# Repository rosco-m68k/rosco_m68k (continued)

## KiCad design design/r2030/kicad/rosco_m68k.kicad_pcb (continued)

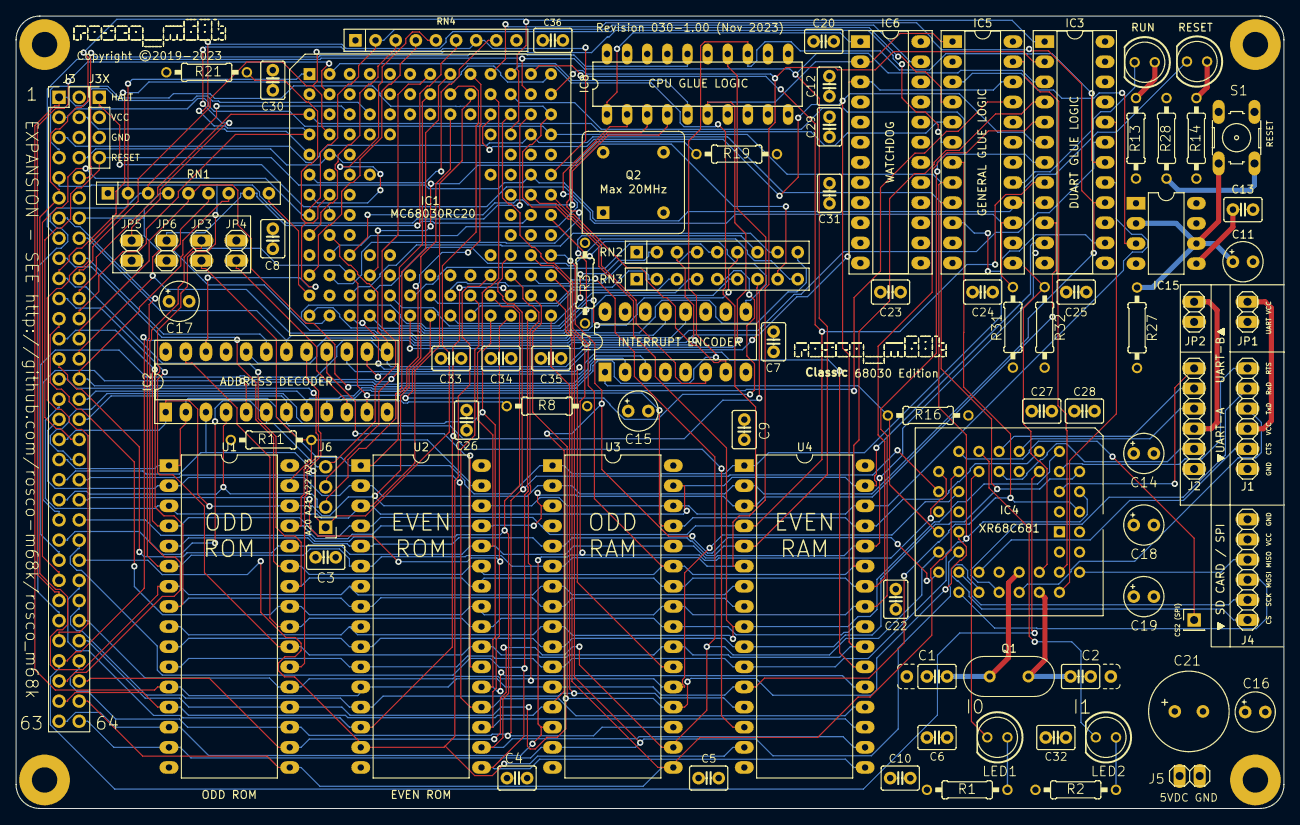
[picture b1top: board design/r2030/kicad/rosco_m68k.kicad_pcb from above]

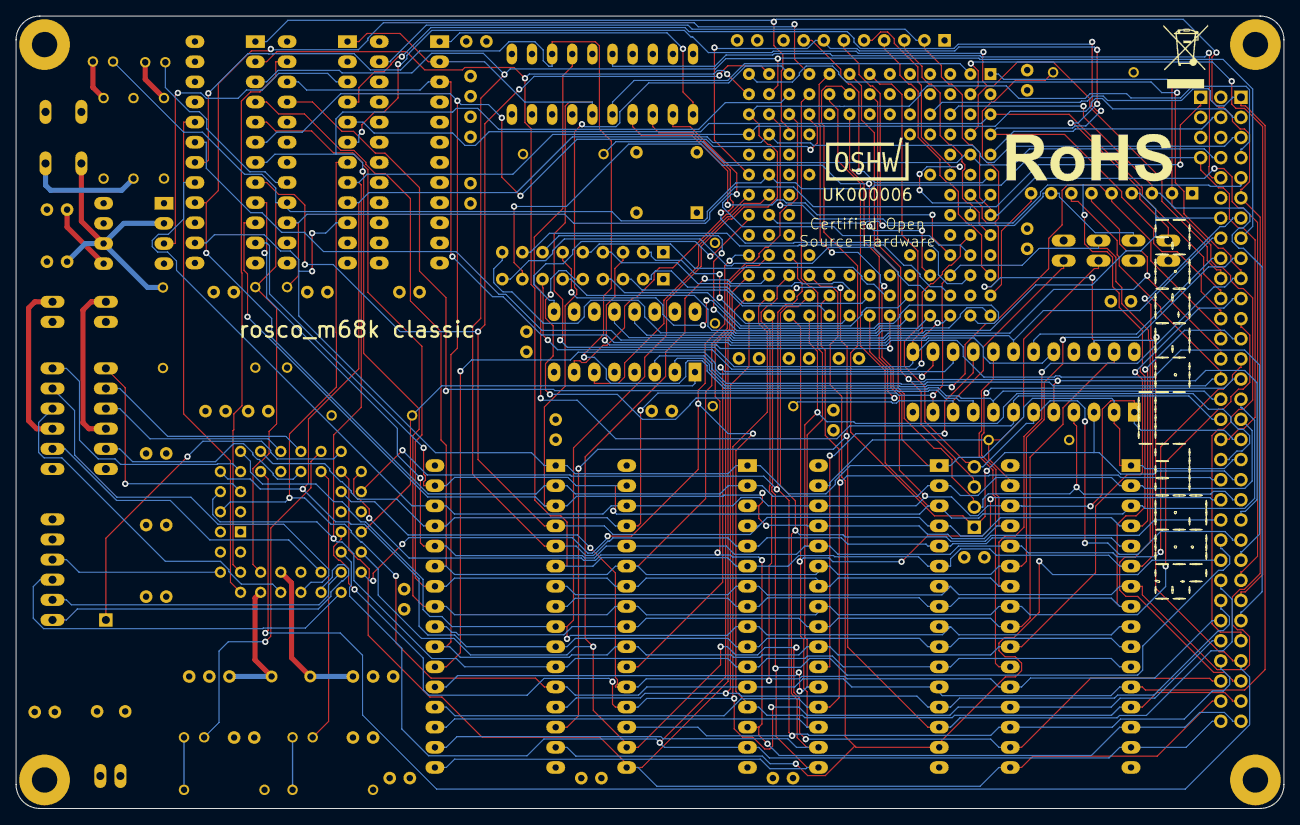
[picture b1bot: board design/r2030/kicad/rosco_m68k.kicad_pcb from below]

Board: 4 copper layers, 160.0 x 100.0 mm, 97 parts (3 on the bottom side), 135 nets.

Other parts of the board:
OSHW_Mono_0.25_Scale: UK000006; OSHW_Mono_0.25_Scale
rohs: RoHS-Logo_6mm_SilkScreen
rosco_m68k, rosco_m68k_mid: SM-rosco_m68k_logo
weee: WEEE-Logo_5.6x8mm_SilkScreen

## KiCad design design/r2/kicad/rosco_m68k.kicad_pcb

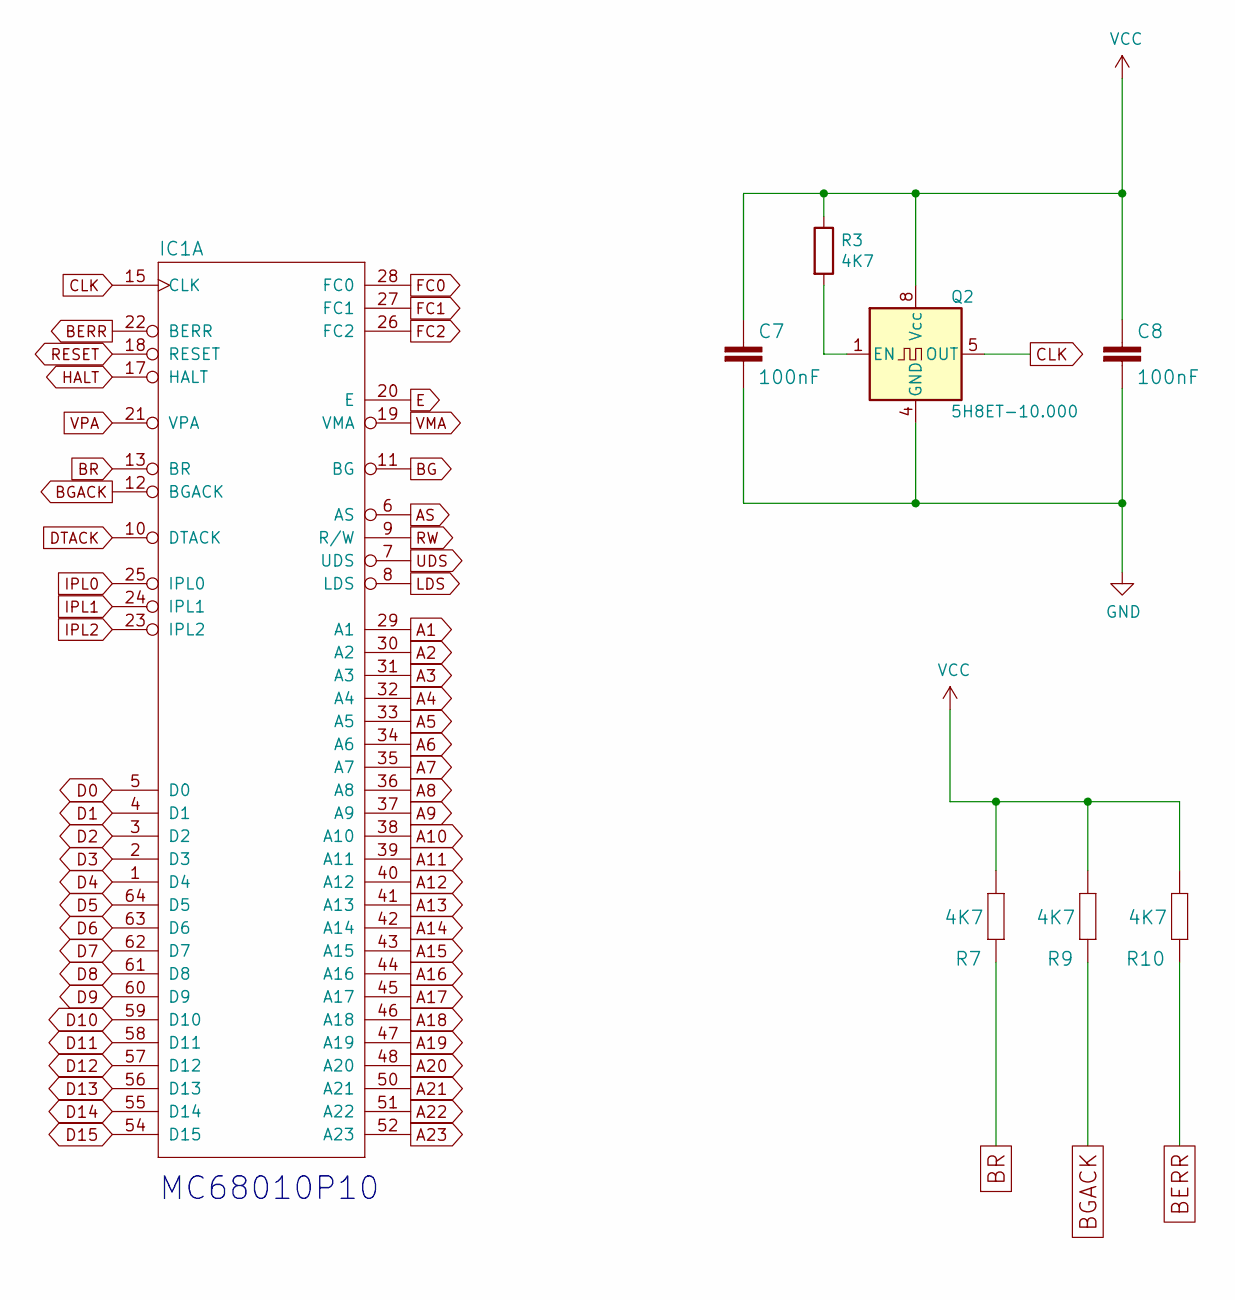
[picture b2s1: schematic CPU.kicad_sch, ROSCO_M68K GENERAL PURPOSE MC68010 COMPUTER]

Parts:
C7, C8: 100nF; C2.5-3
IC1: MC68010P10; DIL64
Q2: 5H8ET-10.000; Oscillator_DIP-8
R3, R7, R9, R10: 4K7; 0207_10

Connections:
A1: IC1.29 (A1); also elsewhere on the board
A2: IC1.30 (A2); also elsewhere on the board
A3: IC1.31 (A3); also elsewhere on the board
A4: IC1.32 (A4); also elsewhere on the board
A5: IC1.33 (A5); also elsewhere on the board
A6: IC1.34 (A6); also elsewhere on the board
A7: IC1.35 (A7); also elsewhere on the board
A8: IC1.36 (A8); also elsewhere on the board
A9: IC1.37 (A9); also elsewhere on the board
A10: IC1.38 (A10); also elsewhere on the board
A11: IC1.39 (A11); also elsewhere on the board
A12: IC1.40 (A12); also elsewhere on the board
A13: IC1.41 (A13); also elsewhere on the board
A14: IC1.42 (A14); also elsewhere on the board
A15: IC1.43 (A15); also elsewhere on the board
A16: IC1.44 (A16); also elsewhere on the board
A17: IC1.45 (A17); also elsewhere on the board
A18: IC1.46 (A18); also elsewhere on the board
A19: IC1.47 (A19); also elsewhere on the board
A20: IC1.48 (A20); also elsewhere on the board
A21: IC1.50 (A21); also elsewhere on the board
A22: IC1.51 (A22); also elsewhere on the board
A23: IC1.52 (A23); also elsewhere on the board
AS: IC1.6 (AS); also elsewhere on the board
BERR: IC1.22 (BERR), R10.1; also elsewhere on the board
BG: IC1.11 (BG); also elsewhere on the board
BGACK: IC1.12 (BGACK), R9.1; also elsewhere on the board
BR: IC1.13 (BR), R7.1; also elsewhere on the board
CLK: IC1.15 (CLK), Q2.5 (OUT); also elsewhere on the board
D0: IC1.5 (D0); also elsewhere on the board
D1: IC1.4 (D1); also elsewhere on the board
D2: IC1.3 (D2); also elsewhere on the board
D3: IC1.2 (D3); also elsewhere on the board
D4: IC1.1 (D4); also elsewhere on the board
D5: IC1.64 (D5); also elsewhere on the board
D6: IC1.63 (D6); also elsewhere on the board
D7: IC1.62 (D7); also elsewhere on the board
D8: IC1.61 (D8); also elsewhere on the board
D9: IC1.60 (D9); also elsewhere on the board
D10: IC1.59 (D10); also elsewhere on the board
D11: IC1.58 (D11); also elsewhere on the board
D12: IC1.57 (D12); also elsewhere on the board
D13: IC1.56 (D13); also elsewhere on the board
D14: IC1.55 (D14); also elsewhere on the board
D15: IC1.54 (D15); also elsewhere on the board
DTACK: IC1.10 (DTACK); also elsewhere on the board
E: IC1.20 (E); also elsewhere on the board
FC0: IC1.28 (FC0); also elsewhere on the board
FC1: IC1.27 (FC1); also elsewhere on the board
FC2: IC1.26 (FC2); also elsewhere on the board
GND: C7.2, C8.2, IC1.16 (GND@1), IC1.53 (GND@2), Q2.4 (GND); also elsewhere on the board
HALT: IC1.17 (HALT); also elsewhere on the board
IPL0: IC1.25 (IPL0); also elsewhere on the board
IPL1: IC1.24 (IPL1); also elsewhere on the board
IPL2: IC1.23 (IPL2); also elsewhere on the board
LDS: IC1.8 (LDS); also elsewhere on the board
unnamed: Q2.1 (EN), R3.2
RESET: IC1.18 (RESET); also elsewhere on the board
RW: IC1.9 (R/W); also elsewhere on the board
UDS: IC1.7 (UDS); also elsewhere on the board
VCC: C7.1, C8.1, IC1.14 (VCC@1), IC1.49 (VCC@2), Q2.8 (Vcc), R3.1, R7.2, R9.2, R10.2; also elsewhere on the board
VMA: IC1.19 (VMA); also elsewhere on the board
VPA: IC1.21 (VPA); also elsewhere on the board

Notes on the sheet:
MC68010P10

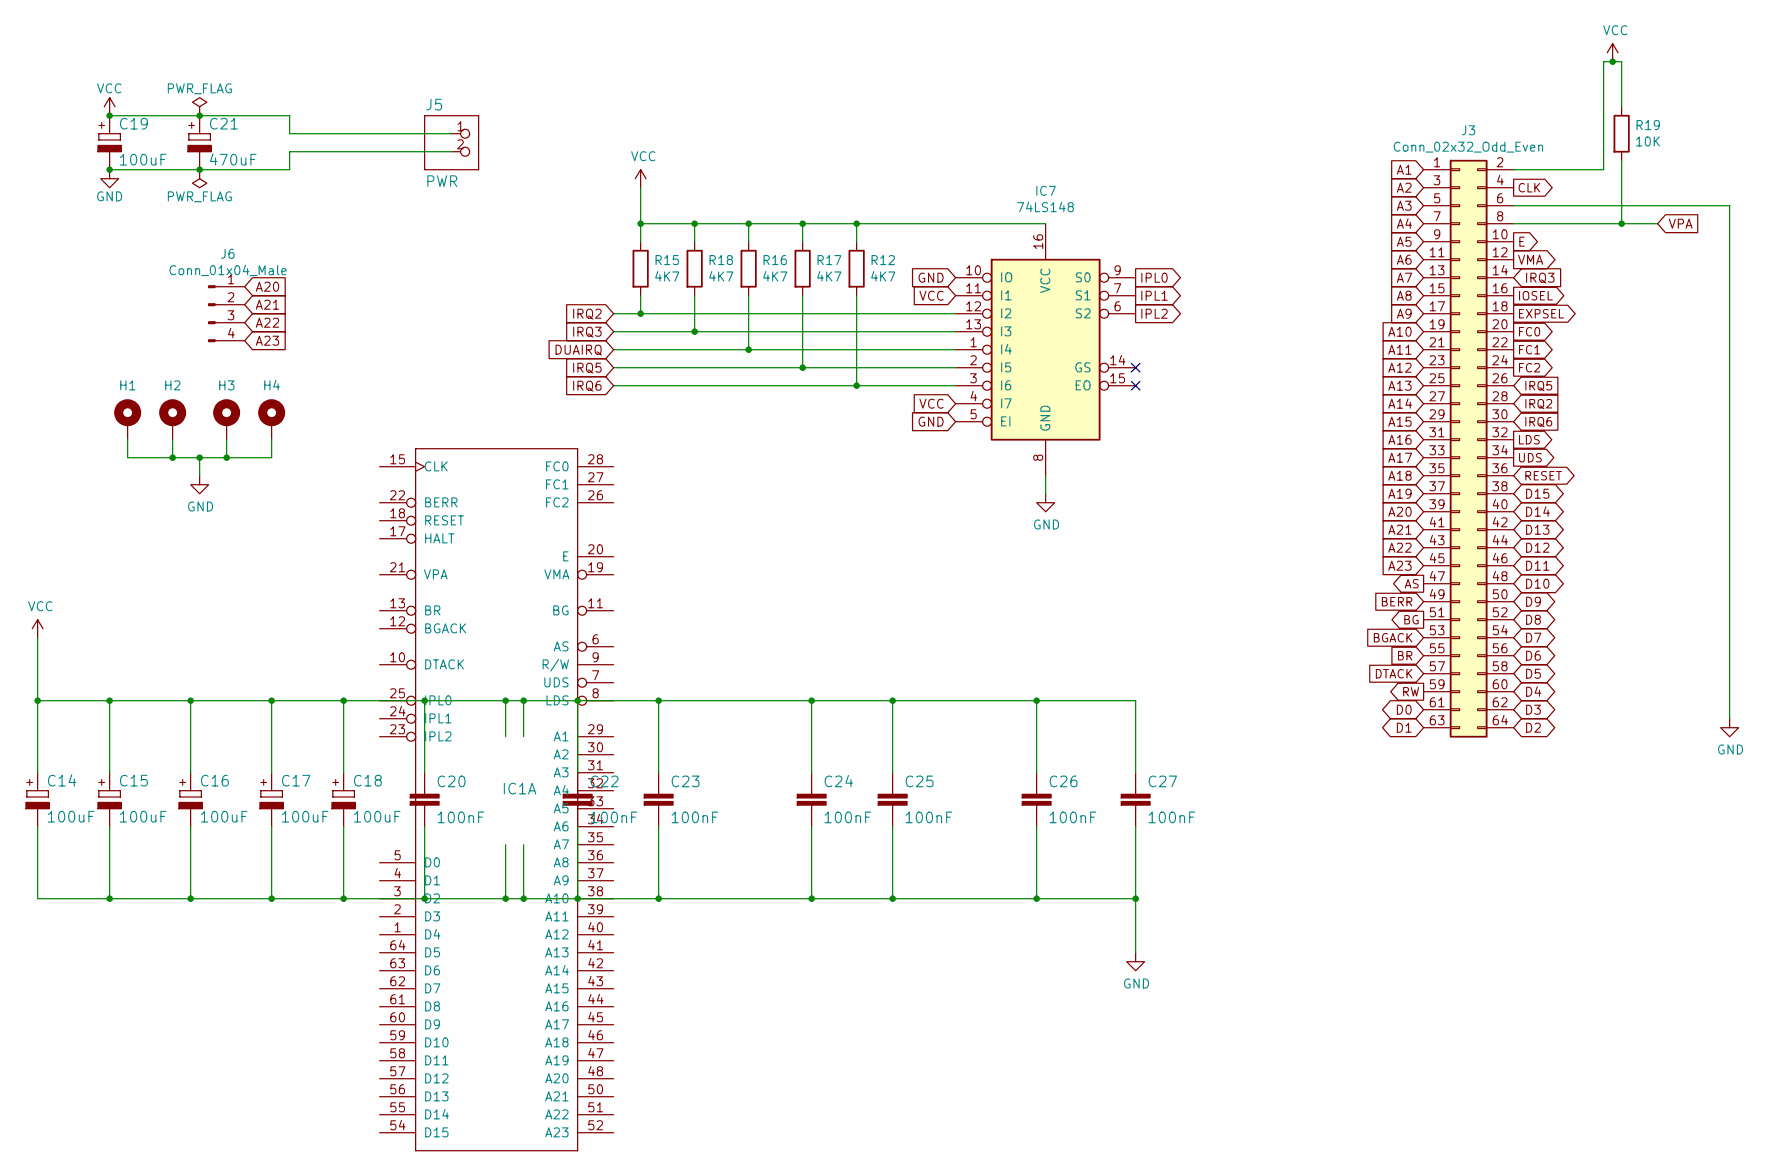
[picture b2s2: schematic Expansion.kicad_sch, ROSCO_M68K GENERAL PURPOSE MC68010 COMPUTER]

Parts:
C14, C15, C16, C17, C18, C19: 100uF; E2,5-5
C20, C22, C23, C24, C25, C26, C27: 100nF; C2.5-3
C21: 470uF; E3,5-10
H1, H2, H3, H4: MountingHole; MountingHole_3.2mm_M3_Pad
IC1: MC68010P10; DIL64
IC7: 74LS148; DIP-16_W7.62mm_LongPads
J3: Conn_02x32_Odd_Even; PinHeader_2x32_P2.54mm_Vertical
J5: PWR; 1X02
J6: Conn_01x04_Male; PinHeader_1x04_P2.54mm_Vertical
R12, R15, R16, R17, R18: 4K7; 0207_10
R19: 10K; 0207_10

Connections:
A1: IC1.29 (A1), J3.1; also elsewhere on the board
A2: IC1.30 (A2), J3.3; also elsewhere on the board
A3: IC1.31 (A3), J3.5; also elsewhere on the board
A4: IC1.32 (A4), J3.7; also elsewhere on the board
A5: IC1.33 (A5), J3.9; also elsewhere on the board
A6: IC1.34 (A6), J3.11; also elsewhere on the board
A7: IC1.35 (A7), J3.13; also elsewhere on the board
A8: IC1.36 (A8), J3.15; also elsewhere on the board
A9: IC1.37 (A9), J3.17; also elsewhere on the board
A10: IC1.38 (A10), J3.19; also elsewhere on the board
A11: IC1.39 (A11), J3.21; also elsewhere on the board
A12: IC1.40 (A12), J3.23; also elsewhere on the board
A13: IC1.41 (A13), J3.25; also elsewhere on the board
A14: IC1.42 (A14), J3.27; also elsewhere on the board
A15: IC1.43 (A15), J3.29; also elsewhere on the board
A16: IC1.44 (A16), J3.31; also elsewhere on the board
A17: IC1.45 (A17), J3.33; also elsewhere on the board
A18: IC1.46 (A18), J3.35; also elsewhere on the board
A19: IC1.47 (A19), J3.37; also elsewhere on the board
A20: IC1.48 (A20), J3.39, J6.1; also elsewhere on the board
A21: IC1.50 (A21), J3.41, J6.2; also elsewhere on the board
A22: IC1.51 (A22), J3.43, J6.3; also elsewhere on the board
A23: IC1.52 (A23), J3.45, J6.4; also elsewhere on the board
AS: IC1.6 (AS), J3.47; also elsewhere on the board
BERR: IC1.22 (BERR), J3.49; also elsewhere on the board
BG: IC1.11 (BG), J3.51
BGACK: IC1.12 (BGACK), J3.53; also elsewhere on the board
BR: IC1.13 (BR), J3.55; also elsewhere on the board
CLK: IC1.15 (CLK), J3.4; also elsewhere on the board
D0: IC1.5 (D0), J3.61; also elsewhere on the board
D1: IC1.4 (D1), J3.63; also elsewhere on the board
D2: IC1.3 (D2), J3.64; also elsewhere on the board
D3: IC1.2 (D3), J3.62; also elsewhere on the board
D4: IC1.1 (D4), J3.60; also elsewhere on the board
D5: IC1.64 (D5), J3.58; also elsewhere on the board
D6: IC1.63 (D6), J3.56; also elsewhere on the board
D7: IC1.62 (D7), J3.54; also elsewhere on the board
D8: IC1.61 (D8), J3.52; also elsewhere on the board
D9: IC1.60 (D9), J3.50; also elsewhere on the board
D10: IC1.59 (D10), J3.48; also elsewhere on the board
D11: IC1.58 (D11), J3.46; also elsewhere on the board
D12: IC1.57 (D12), J3.44; also elsewhere on the board
D13: IC1.56 (D13), J3.42; also elsewhere on the board
D14: IC1.55 (D14), J3.40; also elsewhere on the board
D15: IC1.54 (D15), J3.38; also elsewhere on the board
DTACK: IC1.10 (DTACK), J3.57; also elsewhere on the board
DUAIRQ: IC7.1 (I4), R16.2; also elsewhere on the board
E: IC1.20 (E), J3.10
EXPSEL: J3.18; also elsewhere on the board
FC0: IC1.28 (FC0), J3.20; also elsewhere on the board
FC1: IC1.27 (FC1), J3.22; also elsewhere on the board
FC2: IC1.26 (FC2), J3.24; also elsewhere on the board
GND: C14.-, C15.-, C16.-, C17.-, C18.-, C19.-, C20.2, C21.-, C22.2, C23.2, C24.2, C25.2, C26.2, C27.2, H1.1, H2.1, H3.1, H4.1, IC1.16 (GND@1), IC1.53 (GND@2), IC7.5 (EI), IC7.8 (GND), IC7.10 (IO), J3.6, J5.2; also elsewhere on the board
HALT: IC1.17 (HALT); also elsewhere on the board
IOSEL: J3.16; also elsewhere on the board
IPL0: IC1.25 (IPL0), IC7.9 (S0)
IPL1: IC1.24 (IPL1), IC7.7 (S1)
IPL2: IC1.23 (IPL2), IC7.6 (S2)
IRQ2: IC7.12 (I2), J3.28, R15.2
IRQ3: IC7.13 (I3), J3.14, R18.2
IRQ5: IC7.2 (I5), J3.26, R17.2
IRQ6: IC7.3 (I6), J3.30, R12.2
LDS: IC1.8 (LDS), J3.32; also elsewhere on the board
RESET: IC1.18 (RESET), J3.36; also elsewhere on the board
RW: IC1.9 (R/W), J3.59; also elsewhere on the board
UDS: IC1.7 (UDS), J3.34; also elsewhere on the board
VCC: C14.+, C15.+, C16.+, C17.+, C18.+, C19.+, C20.1, C21.+, C22.1, C23.1, C24.1, C25.1, C26.1, C27.1, IC1.14 (VCC@1), IC1.49 (VCC@2), IC7.4 (I7), IC7.11 (I1), IC7.16 (VCC), J3.2, J5.1, R12.1, R15.1, R16.1, R17.1, R18.1, R19.1; also elsewhere on the board
VMA: IC1.19 (VMA), J3.12
VPA: IC1.21 (VPA), J3.8, R19.2

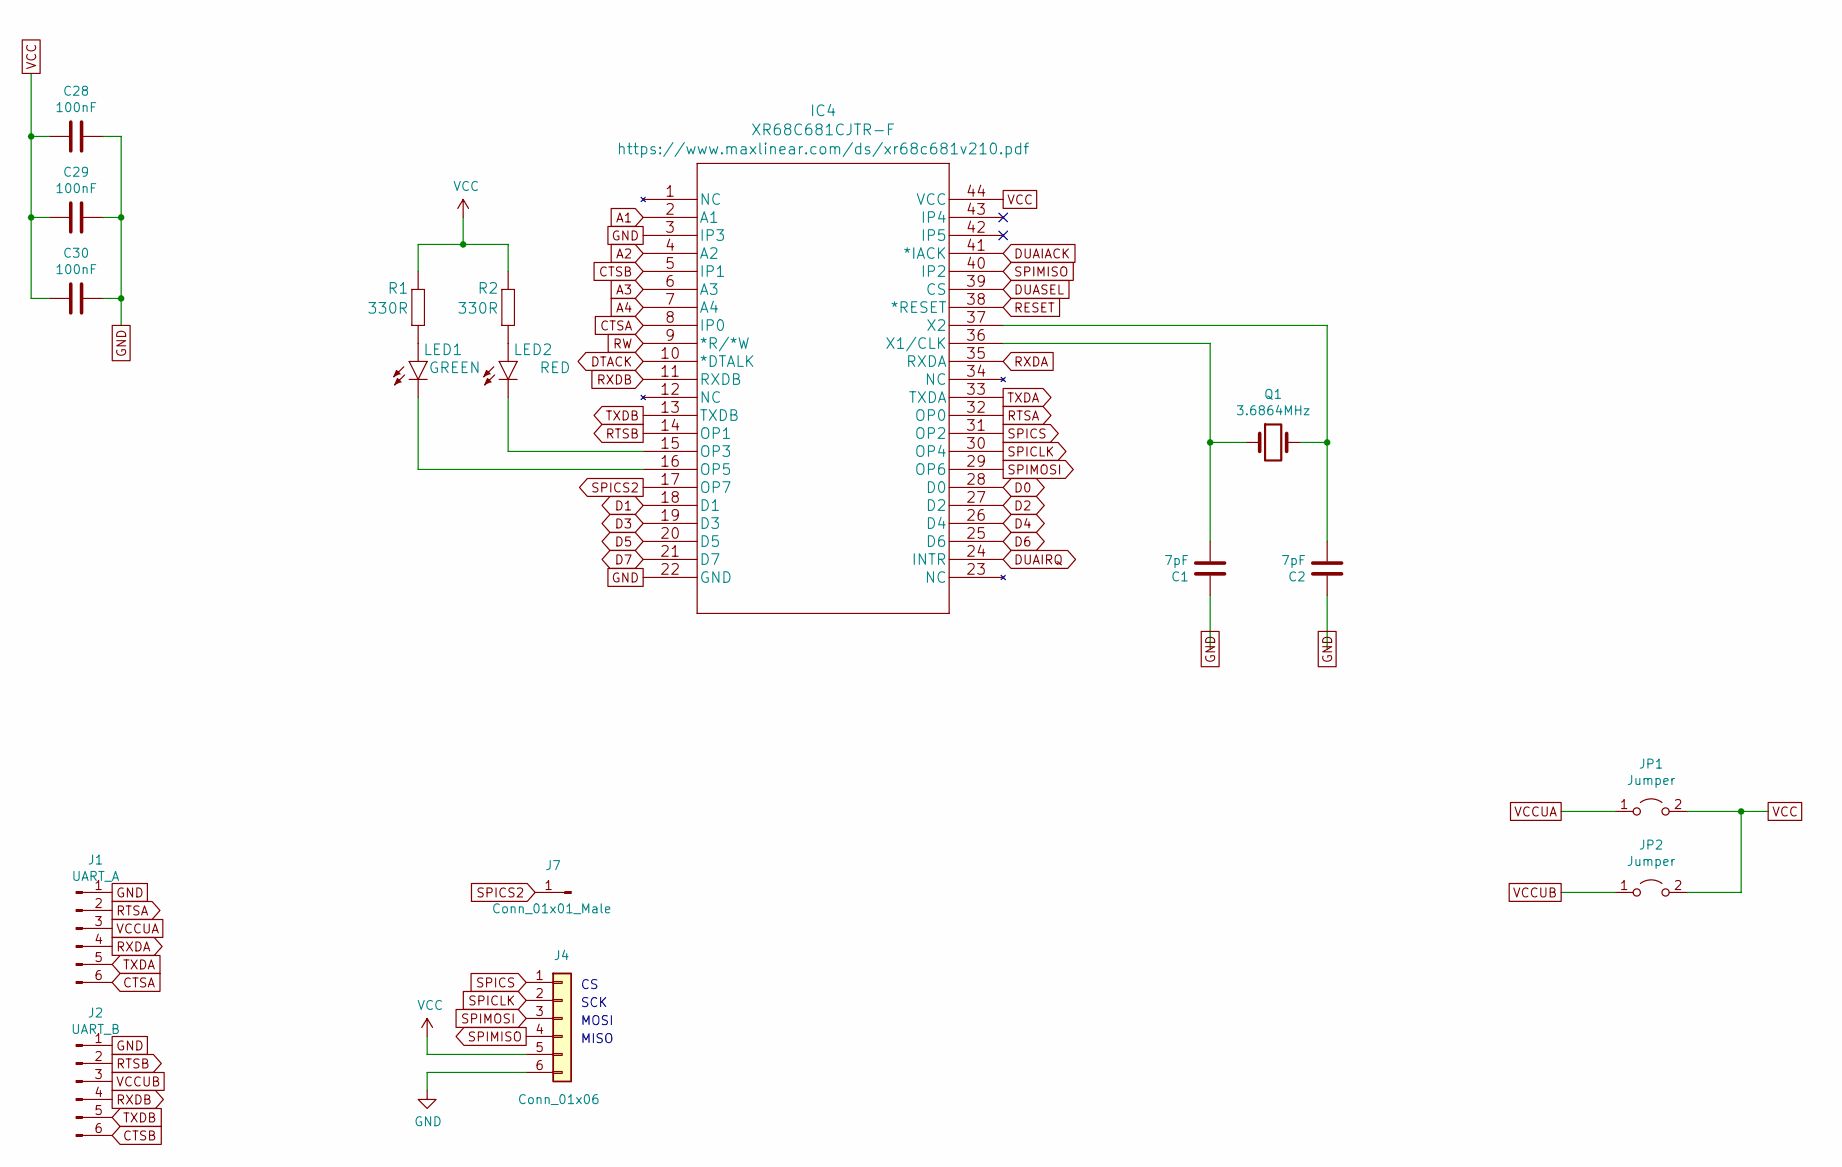
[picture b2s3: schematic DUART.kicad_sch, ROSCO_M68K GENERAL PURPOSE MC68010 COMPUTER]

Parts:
C1, C2: 7pF; C2.5_or_3.5-3
C28, C29, C30: 100nF; C2.5-3
IC4: XR68C681CJTR-F; PLCC-44_THT-Socket
J1: UART_A; 1X06
J2: UART_B; 1X06
J4: Conn_01x06; 1X06
J7: Conn_01x01_Male; PinHeader_1x01_P2.54mm_Vertical
JP1, JP2: Jumper; 1X02
LED1: GREEN; LED5MM
LED2: RED; LED5MM
Q1: 3.6864MHz; Crystal_HC49-4H_Vertical
R1, R2: 330R; 0207_10

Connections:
A1: IC4.2 (A1); also elsewhere on the board
A2: IC4.4 (A2); also elsewhere on the board
A3: IC4.6 (A3); also elsewhere on the board
A4: IC4.7 (A4); also elsewhere on the board
CTSA: IC4.8 (IP0), J1.6
CTSB: IC4.5 (IP1), J2.6
D0: IC4.28 (D0); also elsewhere on the board
D1: IC4.18 (D1); also elsewhere on the board
D2: IC4.27 (D2); also elsewhere on the board
D3: IC4.19 (D3); also elsewhere on the board
D4: IC4.26 (D4); also elsewhere on the board
D5: IC4.20 (D5); also elsewhere on the board
D6: IC4.25 (D6); also elsewhere on the board
D7: IC4.21 (D7); also elsewhere on the board
DTACK: IC4.10 (*DTALK); also elsewhere on the board
DUAIACK: IC4.41 (*IACK); also elsewhere on the board
DUAIRQ: IC4.24 (INTR); also elsewhere on the board
DUASEL: IC4.39 (CS); also elsewhere on the board
GND: C1.1, C2.1, C28.1, C29.1, C30.1, IC4.3 (IP3), IC4.22 (GND), J1.1, J2.1, J4.6; also elsewhere on the board
unnamed: C1.2, IC4.36 (X1/CLK), Q1.1
unnamed: C2.2, IC4.37 (X2), Q1.2
unnamed: IC4.15 (OP3), LED2.K (C)
unnamed: IC4.16 (OP5), LED1.K (C)
unnamed: LED1.A, R1.1
unnamed: LED2.A, R2.1
RESET: IC4.38 (*RESET); also elsewhere on the board
RTSA: IC4.32 (OP0), J1.2
RTSB: IC4.14 (OP1), J2.2
RW: IC4.9 (*R/*W); also elsewhere on the board
RXDA: IC4.35 (RXDA), J1.4
RXDB: IC4.11 (RXDB), J2.4
SPICLK: IC4.30 (OP4), J4.2
SPICS: IC4.31 (OP2), J4.1
SPICS2: IC4.17 (OP7), J7.1
SPIMISO: IC4.40 (IP2), J4.4
SPIMOSI: IC4.29 (OP6), J4.3
TXDA: IC4.33 (TXDA), J1.5
TXDB: IC4.13 (TXDB), J2.5
VCC: C28.2, C29.2, C30.2, IC4.44 (VCC), J4.5, JP1.2 (B), JP2.2 (B), R1.2, R2.2; also elsewhere on the board
VCCUA: J1.3, JP1.1 (A)
VCCUB: J2.3, JP2.1 (A)

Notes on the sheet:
MISO
SCK
MOSI

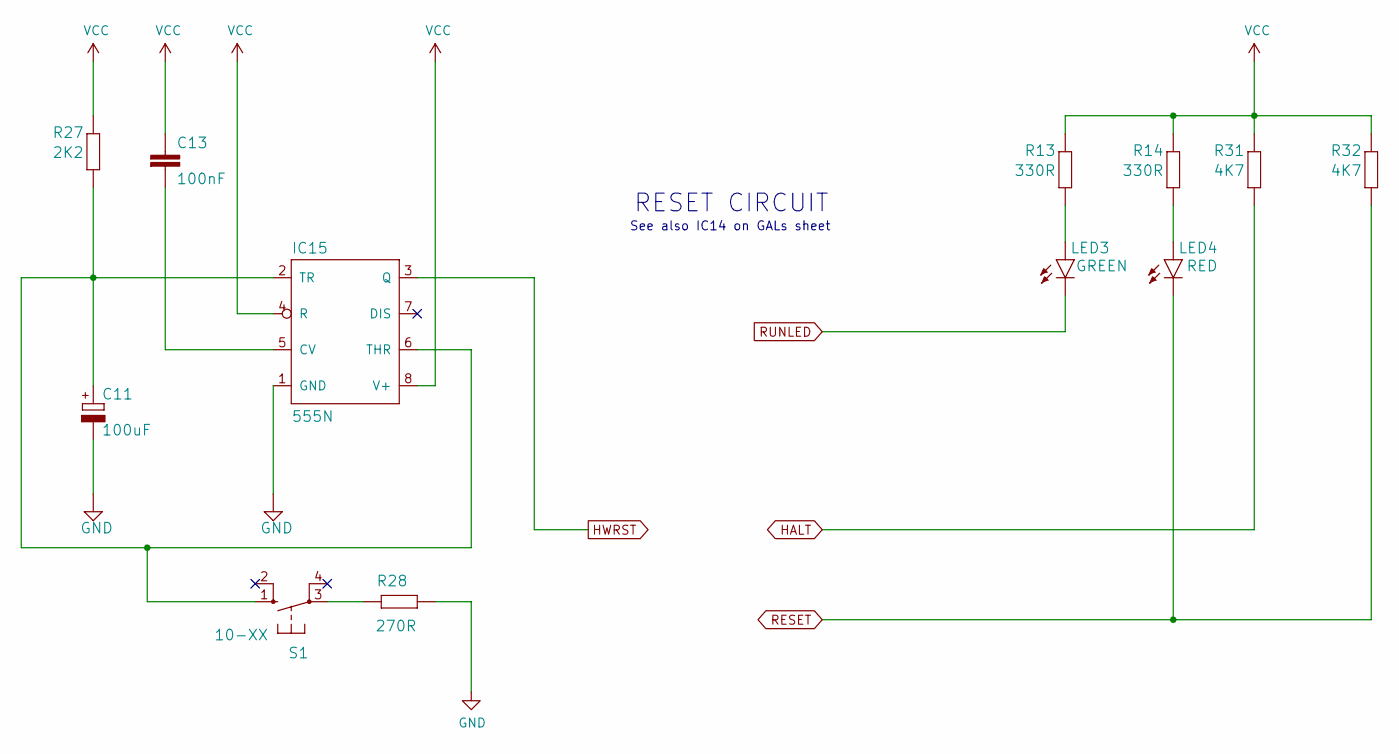
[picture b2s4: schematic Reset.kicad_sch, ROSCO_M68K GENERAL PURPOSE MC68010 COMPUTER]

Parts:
C11: 100uF; E2,5-5
C13: 100nF; C2.5-3
IC15: 555N; DIP-8_W7.62mm_LongPads
LED3: GREEN; LED5MM
LED4: RED; LED5MM
R13, R14: 330R; 0207_10
R27: 2K2; 0207_10
R28: 270R; 0207_10
R31, R32: 4K7; 0207_10
S1: 10-XX; B3F-10XX

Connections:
GND: C11.-, IC15.1 (GND), R28.1; also elsewhere on the board
HALT: R31.1; also elsewhere on the board
HWRST: IC15.3 (Q); also elsewhere on the board
unnamed: C11.+, IC15.2 (TR), IC15.6 (THR), R27.1, S1.1 (S)
unnamed: C13.2, IC15.5 (CV)
unnamed: LED3.A, R13.1
unnamed: LED4.A, R14.1
unnamed: R28.2, S1.3
RESET: LED4.K (C), R32.1; also elsewhere on the board
RUNLED: LED3.K (C); also elsewhere on the board
VCC: C13.1, IC15.4 (R), IC15.8 (V+), R13.2, R14.2, R27.2, R31.2, R32.2; also elsewhere on the board

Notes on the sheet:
See also IC14 on GALs sheet
RESET CIRCUIT

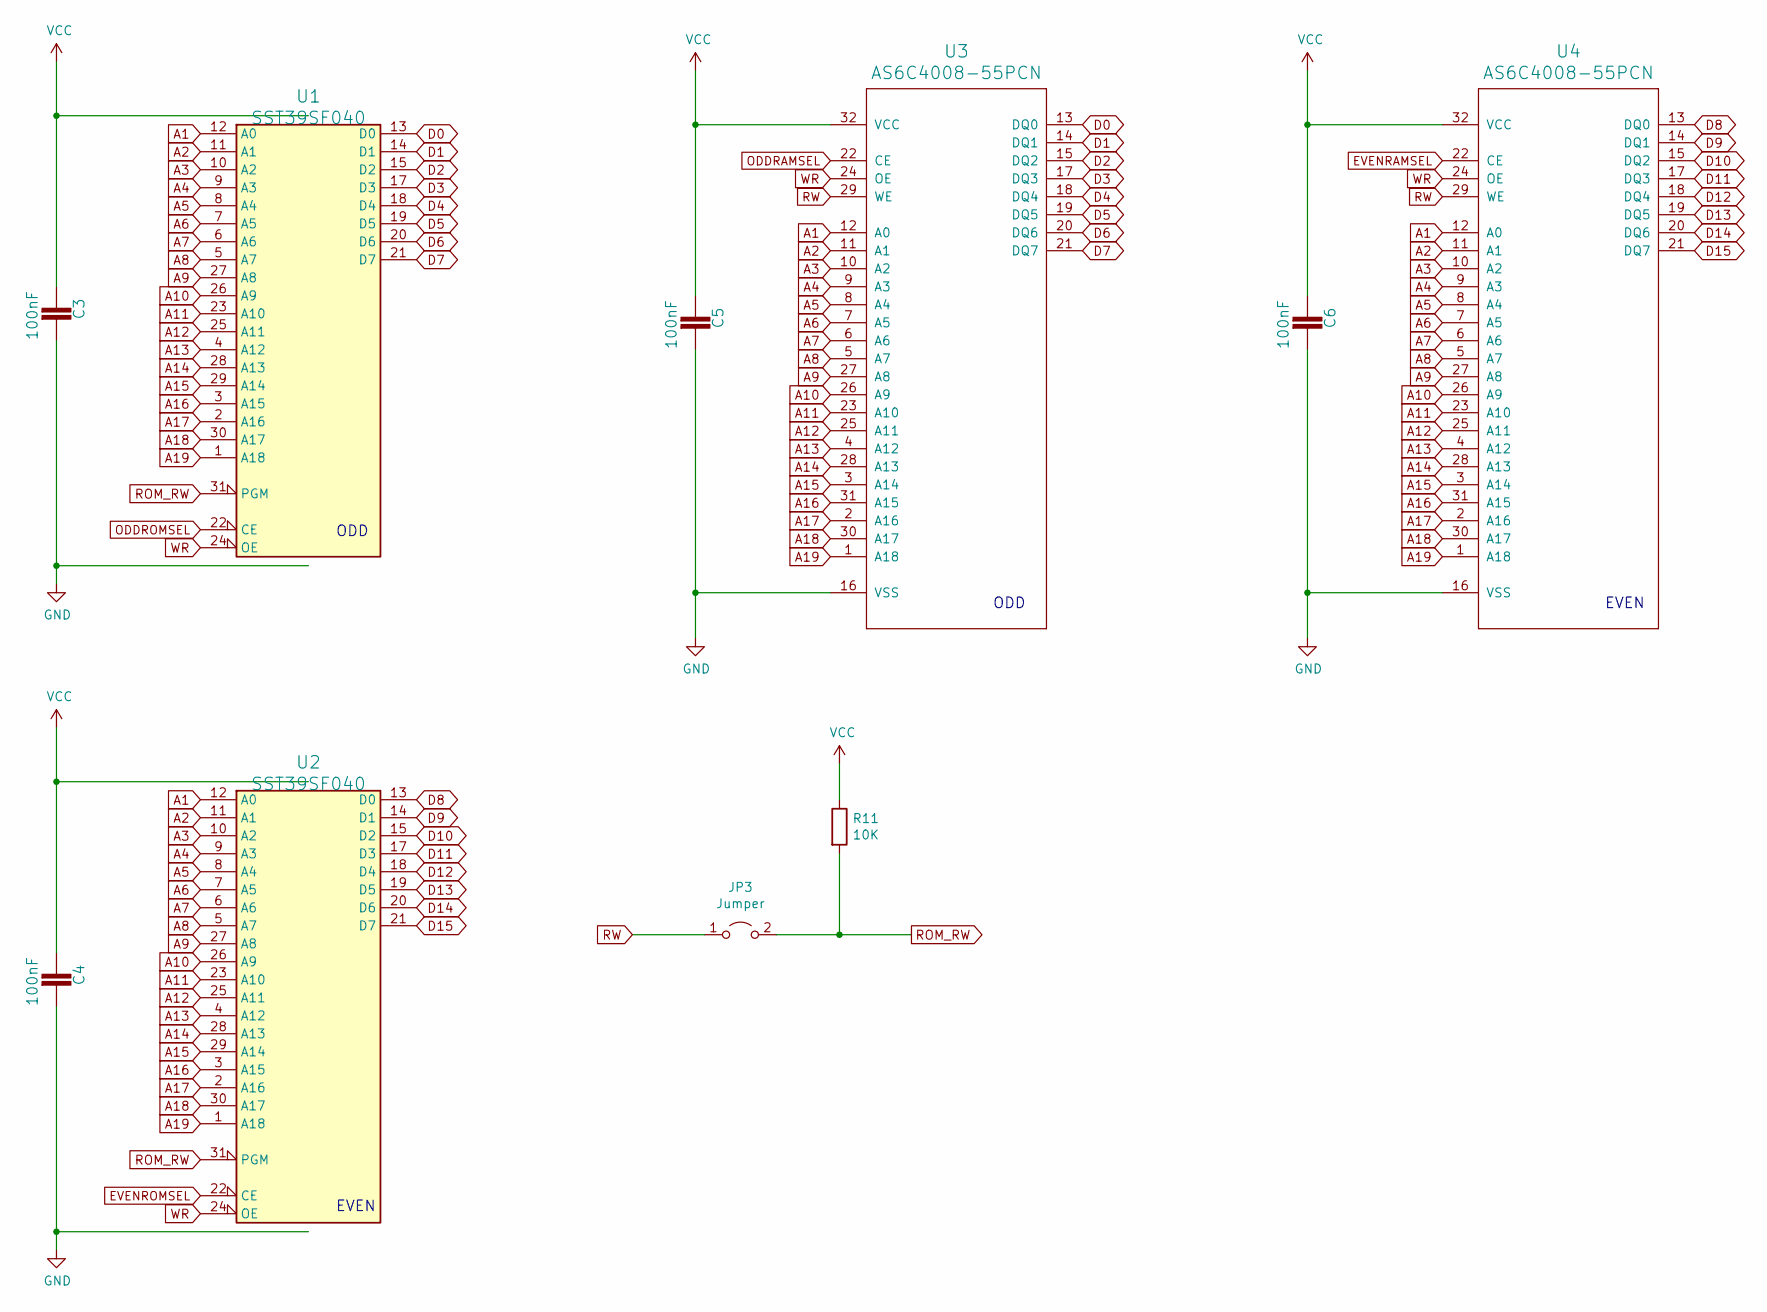
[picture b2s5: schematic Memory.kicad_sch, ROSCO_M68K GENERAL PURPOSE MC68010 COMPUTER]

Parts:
C3, C4, C5, C6: 100nF; C2.5-3
JP3: Jumper; 1X02
R11: 10K; 0207_10
U1, U2: SST39SF040; DIP-32_W15.24mm_LongPads
U3, U4: AS6C4008-55PCN; DIP-32_W15.24mm_LongPads

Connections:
A1: U1.12 (A0), U2.12 (A0), U3.12 (A0), U4.12 (A0); also elsewhere on the board
A2: U1.11 (A1), U2.11 (A1), U3.11 (A1), U4.11 (A1); also elsewhere on the board
A3: U1.10 (A2), U2.10 (A2), U3.10 (A2), U4.10 (A2); also elsewhere on the board
A4: U1.9 (A3), U2.9 (A3), U3.9 (A3), U4.9 (A3); also elsewhere on the board
A5: U1.8 (A4), U2.8 (A4), U3.8 (A4), U4.8 (A4); also elsewhere on the board
A6: U1.7 (A5), U2.7 (A5), U3.7 (A5), U4.7 (A5); also elsewhere on the board
A7: U1.6 (A6), U2.6 (A6), U3.6 (A6), U4.6 (A6); also elsewhere on the board
A8: U1.5 (A7), U2.5 (A7), U3.5 (A7), U4.5 (A7); also elsewhere on the board
A9: U1.27 (A8), U2.27 (A8), U3.27 (A8), U4.27 (A8); also elsewhere on the board
A10: U1.26 (A9), U2.26 (A9), U3.26 (A9), U4.26 (A9); also elsewhere on the board
A11: U1.23 (A10), U2.23 (A10), U3.23 (A10), U4.23 (A10); also elsewhere on the board
A12: U1.25 (A11), U2.25 (A11), U3.25 (A11), U4.25 (A11); also elsewhere on the board
A13: U1.4 (A12), U2.4 (A12), U3.4 (A12), U4.4 (A12); also elsewhere on the board
A14: U1.28 (A13), U2.28 (A13), U3.28 (A13), U4.28 (A13); also elsewhere on the board
A15: U1.29 (A14), U2.29 (A14), U3.3 (A14), U4.3 (A14); also elsewhere on the board
A16: U1.3 (A15), U2.3 (A15), U3.31 (A15), U4.31 (A15); also elsewhere on the board
A17: U1.2 (A16), U2.2 (A16), U3.2 (A16), U4.2 (A16); also elsewhere on the board
A18: U1.30 (A17), U2.30 (A17), U3.30 (A17), U4.30 (A17); also elsewhere on the board
A19: U1.1 (A18), U2.1 (A18), U3.1 (A18), U4.1 (A18); also elsewhere on the board
D0: U1.13 (D0), U3.13 (DQ0); also elsewhere on the board
D1: U1.14 (D1), U3.14 (DQ1); also elsewhere on the board
D2: U1.15 (D2), U3.15 (DQ2); also elsewhere on the board
D3: U1.17 (D3), U3.17 (DQ3); also elsewhere on the board
D4: U1.18 (D4), U3.18 (DQ4); also elsewhere on the board
D5: U1.19 (D5), U3.19 (DQ5); also elsewhere on the board
D6: U1.20 (D6), U3.20 (DQ6); also elsewhere on the board
D7: U1.21 (D7), U3.21 (DQ7); also elsewhere on the board
D8: U2.13 (D0), U4.13 (DQ0); also elsewhere on the board
D9: U2.14 (D1), U4.14 (DQ1); also elsewhere on the board
D10: U2.15 (D2), U4.15 (DQ2); also elsewhere on the board
D11: U2.17 (D3), U4.17 (DQ3); also elsewhere on the board
D12: U2.18 (D4), U4.18 (DQ4); also elsewhere on the board
D13: U2.19 (D5), U4.19 (DQ5); also elsewhere on the board
D14: U2.20 (D6), U4.20 (DQ6); also elsewhere on the board
D15: U2.21 (D7), U4.21 (DQ7); also elsewhere on the board
EVENRAMSEL: U4.22 (CE); also elsewhere on the board
EVENROMSEL: U2.22 (CE); also elsewhere on the board
GND: C3.2, C4.2, C5.2, C6.2, U1.16 (GND), U2.16 (GND), U3.16 (VSS), U4.16 (VSS); also elsewhere on the board
ODDRAMSEL: U3.22 (CE); also elsewhere on the board
ODDROMSEL: U1.22 (CE); also elsewhere on the board
ROM_RW: JP3.2 (B), R11.2, U1.31 (PGM), U2.31 (PGM)
RW: JP3.1 (A), U3.29 (WE), U4.29 (WE); also elsewhere on the board
VCC: C3.1, C4.1, C5.1, C6.1, R11.1, U1.32 (VCC), U2.32 (VCC), U3.32 (VCC), U4.32 (VCC); also elsewhere on the board
WR: U1.24 (OE), U2.24 (OE), U3.24 (OE), U4.24 (OE); also elsewhere on the board

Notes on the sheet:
EVEN
ODD
